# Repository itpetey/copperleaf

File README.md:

# Copperleaf

A typed, constraint-driven Rust EDA library. Copperleaf describes components and
boards in Rust, compiles the design into an auditable net model, and emits a
complete KiCad project.

## Architecture

| Crate | Responsibility |
|-------|----------------|

| `crates/core` | Board builder, components, pins, pads, nets, stackup, units, ERC, and compiled-board validation. |
| `crates/compile` | Lowers a `Board` into a `CompiledBoard`, infers nets, runs ERC, validates, and synthesises decoupling capacitors. |
| `crates/layout` | Placement-only solver and layout design-rule checks. It does not route. |
| `crates/backend-kicad` | Emits `.kicad_pro`, `.kicad_sch`, `.kicad_pcb`, and `.net`, plus standalone `.kicad_sym`/`.kicad_mod` files. |
| `crates/part-codegen` | Generates typed Rust component crates from TOML manifests. |
| `crates/part-macro` | `build_component!` proc-macro entry point for generated parts. |
| `crates/cli` | `cl` parts-creation CLI (`new`, `update`, `generate`). |
| `parts/*` | Generated component libraries, one crate per vendor. |

The compilation path is:

```text
Board -> copperleaf_compile::run -> CompiledBoard -> Backend
```

`CompiledBoard` validation runs after synthesis and again before any backend
writes a file, so an invalid refdes, pin identity, net, dimension, layer, or
stackup cannot produce output.

## Prerequisites

- Rust stable with edition 2024 support (the committed `Cargo.lock` is used).
- Optional: `kicad-cli` 10.0.7 for external acceptance (`docs/acceptance.md`).
- Optional: `cargo-deny`, `cargo-shear`, and the OpenSpec CLI for the full
  verification workflow.

## Build and test

```sh
cargo build --workspace --all-targets --locked
cargo test --workspace --locked
cargo fmt --all -- --check
cargo clippy --workspace --all-targets --locked -- -D warnings
RUSTDOCFLAGS="-D warnings" cargo doc --workspace --no-deps --locked
```

## CLI examples

Create a part from a KiCad symbol:

```sh
cargo run -p copperleaf-cli -- new --symbol ic.kicad_sym \
  --lib-id RP2354A --crate raspberrypi
```

Create a part from a footprint or a directory containing both sources:

```sh
cargo run -p copperleaf-cli -- new --footprint ic.kicad_mod \
  --lib-id TEST --out test.toml
cargo run -p copperleaf-cli -- new --dir ./part_files/ \
  --lib-id TEST --crate testvendor
```

Update an existing vendor part from its symbol or footprint:

```sh
cargo run -p copperleaf-cli -- update --crate raspberrypi --lib-id RP2354A \
  --symbol ic.kicad_sym
```

Generate standalone KiCad library files from a manifest:

```sh
cargo run -p copperleaf-cli -- generate symbol parts/microchip/mcp73831t_2ati_ot.toml
cargo run -p copperleaf-cli -- generate footprint parts/microchip/mcp73831t_2ati_ot.toml
```

Datasheet mode requires the local `opencode` CLI and a configured provider:

```sh
cargo run -p copperleaf-cli -- new --datasheet datasheet.pdf --out part.toml
```

A small board can be built and emitted with the library API:

```rust
use copperleaf::{Backend, Board};
use copperleaf_backend_kicad::KiCad;

let mut board = Board::new("demo");
let u1 = board.add("U1", copperleaf_parts_wiznet::W5500::new());
let r1 = board.add(
    "R1",
    copperleaf_parts_passives::Resistor::new(
        33.0.kohm(),
        copperleaf_parts_passives::footprint::Package::M1608,
    ),
);
board.connect(u1.pin(copperleaf_parts_wiznet::W5500::GND), r1.pin(copperleaf_parts_passives::Resistor::PIN1))?;

let report = copperleaf_compile::run(board, &copperleaf_compile::CompileOptions::default())?;
KiCad::new().with_project_name("demo").emit("output", &report.board)?;
```

(Import `copperleaf::UnitExt` for `.kohm()`.)

## Supported capabilities

- Typed, compile-checked board construction with physical pin identity.
- Net inference, ERC, overvoltage and NC checks.
- Deterministic decoupling-capacitor synthesis and collision-free refdes allocation.
- Central compiled-board validation that blocks invalid emission.
- KiCad 10 project emission with schematic, netlist, PCB, footprints, and models.
- Deterministic UUIDs and byte-reproducible output.
- Placement-only layout solving with layout DRC.
- Manifest-to-Rust generation with typed quantities and escaped literals.
- Reviewed KiCad ERC/DRC/schematic-parity acceptance for a representative board.

## Unsupported capabilities

- Autorouting, track optimisation, and differential-pair or impedance tuning.
- Full fabrication sign-off, thermal simulation, and signal-integrity analysis.
- Automatic resolution of arbitrary external KiCad libraries at compile time.
- Release publication: every workspace package is explicitly unpublished.
- LLM-produced manifests are draft input only.

## Verification

The full gate set is documented in `docs/acceptance.md` for KiCad and below for
the workspace:

```sh
cargo build --workspace --all-targets --locked
cargo test --workspace --locked
cargo fmt --all -- --check
cargo clippy --workspace --all-targets --locked -- -D warnings
RUSTDOCFLAGS="-D warnings" cargo doc --workspace --no-deps --locked
openspec validate --specs --strict
cargo deny check
cargo shear
./scripts/kicad-acceptance.sh
```

CI runs the same locked build, format, Clippy, rustdoc, tests, and the pinned
KiCad acceptance job. Tests never bless snapshots in CI; creating or updating a
golden requires `COPPERLEAF_BLESS=1`.

## Trust boundaries

- Part manifests and generated Rust are treated as untrusted input.
- Strings are escaped through a Rust literal API and identifiers are validated.
- Datasheet text is sent to the configured model provider; the provider may
  retain it, and datasheets can contain prompt-injection text. Treat LLM output
  as a reviewable draft. Generated output is never compiled automatically.
- Backend output paths are contained beneath the destination directory; absolute
  paths, traversal, and symlink escapes are rejected before writing.
- Embedded 3D-model data is optional; empty payloads are rejected rather than
  written as zero-length files.

## Licence

Copperleaf is licensed under the Mozilla Public License 2.0. See
[`LICENCE`](LICENCE).

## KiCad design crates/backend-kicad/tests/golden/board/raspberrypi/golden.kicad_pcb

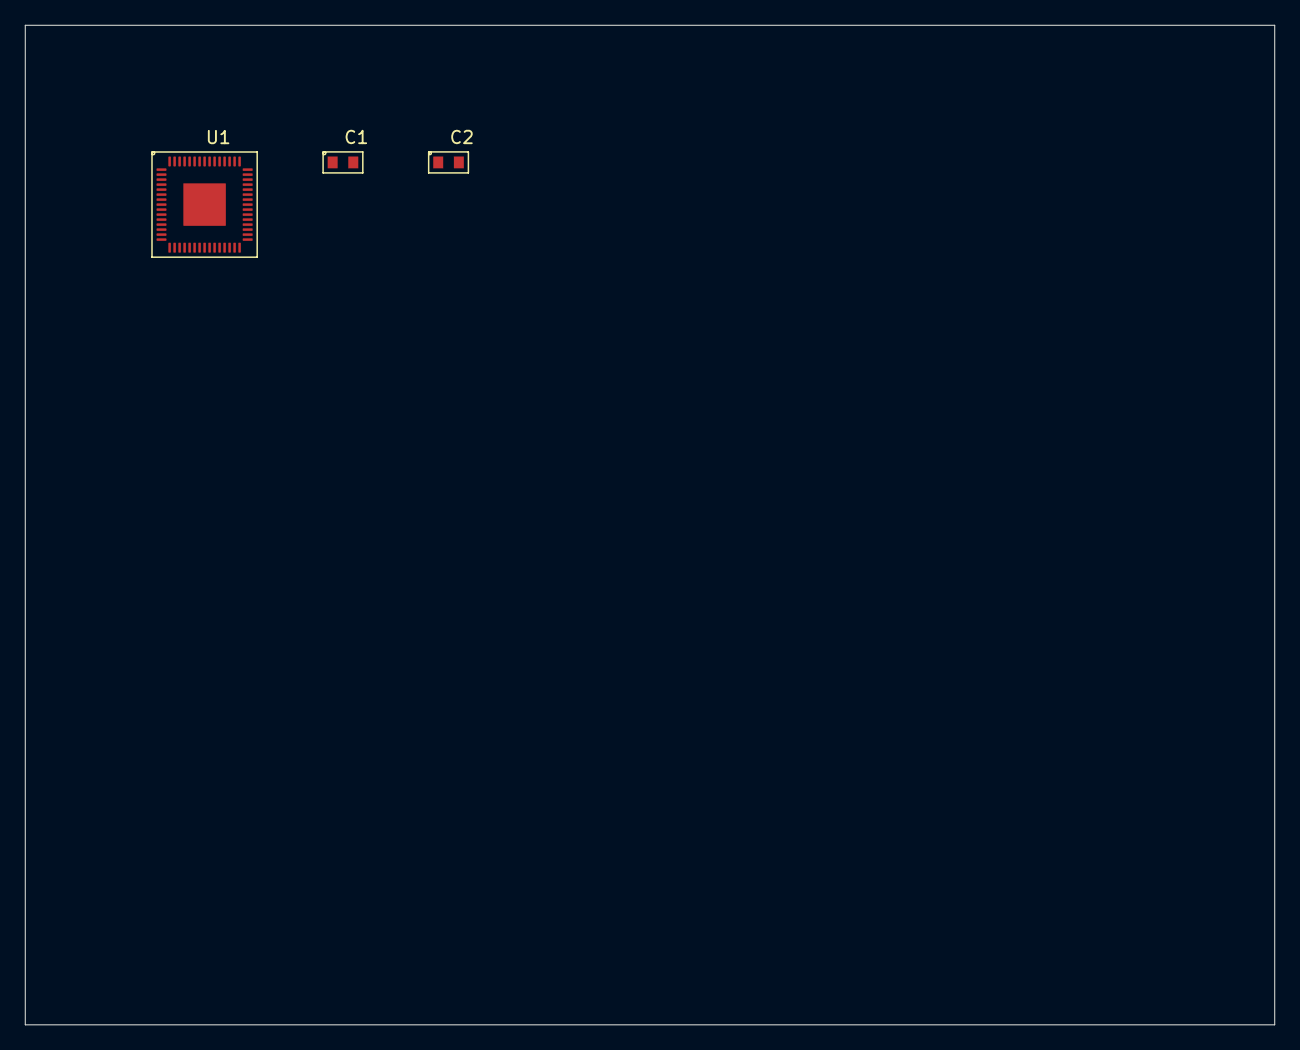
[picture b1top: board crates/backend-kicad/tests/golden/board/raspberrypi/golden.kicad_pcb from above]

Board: 2 copper layers, 100.0 x 80.0 mm, 3 parts (0 on the bottom side), 2 nets, no tracks yet.

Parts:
C1, C2: C; C_0603_1608Metric
U1: U; RP2354A

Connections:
NET_U1_ADC_AVDD: C1.1, C2.1, U1.44, U1.53
NET_U1_VREG_PGND: C1.2, C2.2, U1.47, U1.61

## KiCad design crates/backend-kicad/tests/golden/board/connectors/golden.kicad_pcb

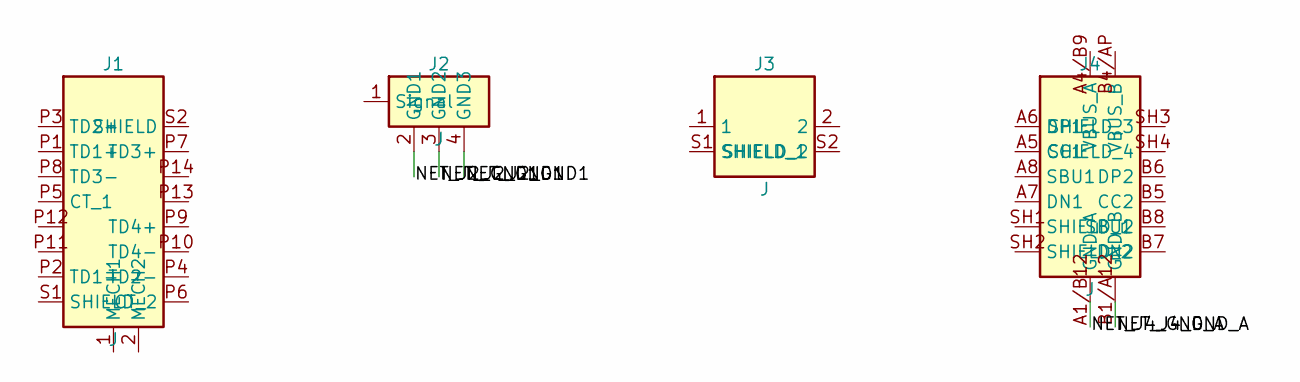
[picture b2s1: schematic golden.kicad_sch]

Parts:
J1: J; ARJM11D7-502-AB-EW2
J2: J; CONMHF4-SMD-G-T
J3: J; S2B-PH-SM4-TB_LF__SN_
J4: J; 2340901-1

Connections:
NET_J2_GND1: J2.2 (GND1), J2.3 (GND2), J2.4 (GND3)
NET_J4_GND_A: J4.A1/B12 (GND_A), J4.B1/A12 (GND_B)

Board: 2 copper layers, 4 parts (0 on the bottom side), 2 nets, no tracks yet.

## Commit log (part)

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2025-09-04 Initial scaffold
2025-09-07 First version
2025-10-05 Docs
